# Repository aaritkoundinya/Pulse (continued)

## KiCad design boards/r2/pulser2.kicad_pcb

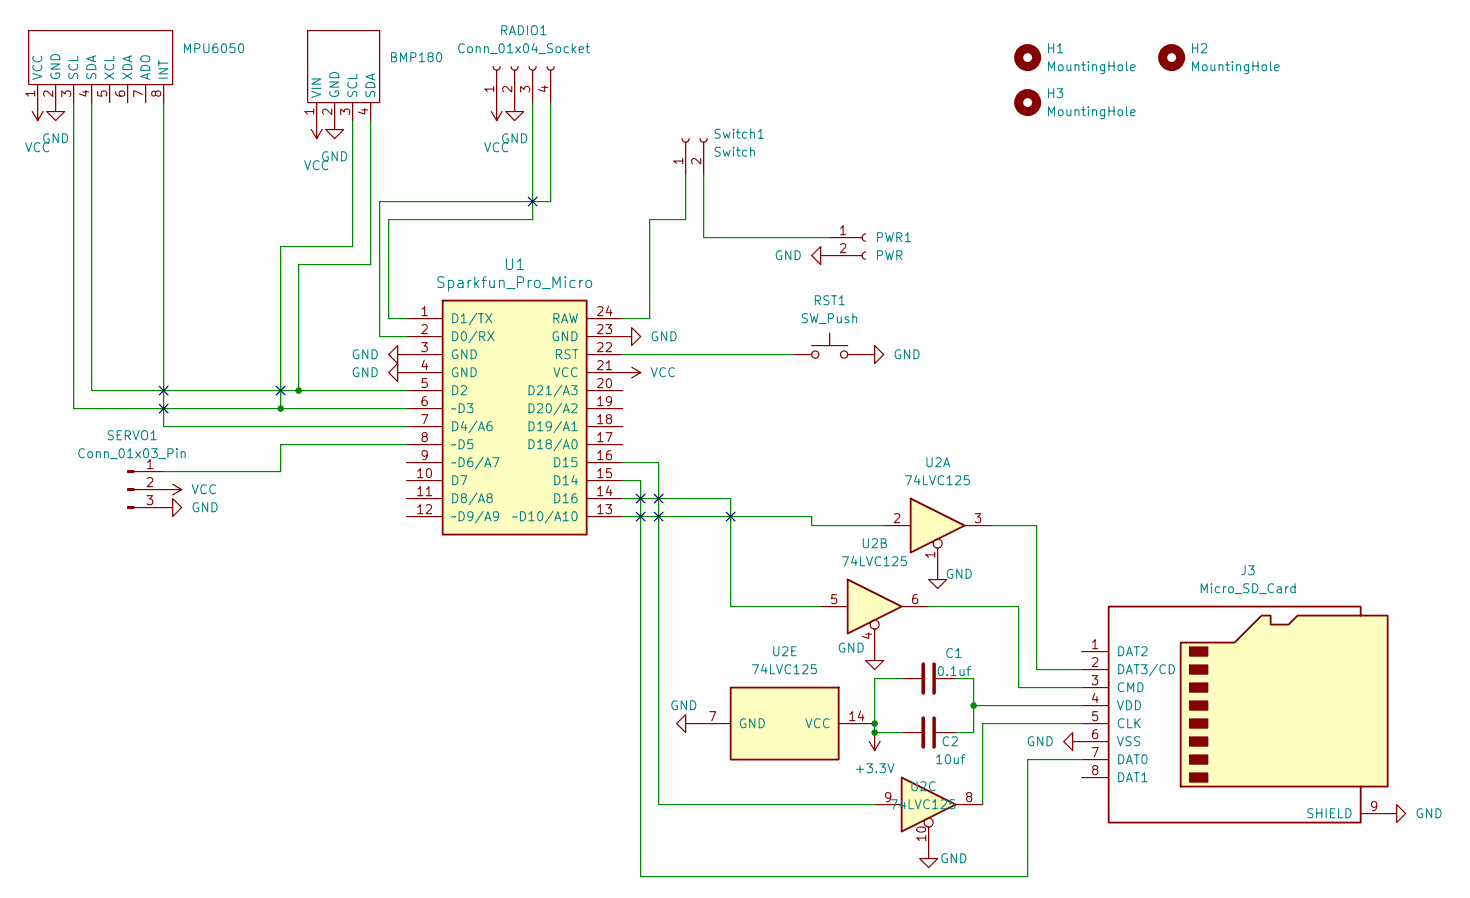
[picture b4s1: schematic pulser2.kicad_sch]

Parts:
BMP180: bmp180
C1: 0.1uf; C_0603_1608Metric_Pad1.08x0.95mm_HandSolder
C2: 10uf; C_0805_2012Metric_Pad1.18x1.45mm_HandSolder
H1, H2, H3: MountingHole; MountingHole_2.2mm_M2
J3: Micro_SD_Card; microSD_HC_Hirose_DM3D-SF
MPU6050: gy521
PWR1: PWR; JST_XH_B2B-XH-A_1x02_P2.50mm_Vertical
RADIO1: Conn_01x04_Socket; JST_XH_B4B-XH-A_1x04_P2.50mm_Vertical
RST1: SW_Push; SW_PUSH_6mm_H5mm
SERVO1: Conn_01x03_Pin; PinHeader_1x03_P2.54mm_Horizontal
Switch1: Switch; JST_XH_B2B-XH-A_1x02_P2.50mm_Vertical
U1: Sparkfun_Pro_Micro
U2: 74LVC125; SOIC-14_3.9x8.7mm_P1.27mm

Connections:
+3.3V: C1.2, C2.2, U2.14 (VCC)
GND: BMP180.2 (GND), J3.6 (VSS), J3.9 (SHIELD), MPU6050.2 (GND), PWR1.2, RADIO1.2, RST1.2, SERVO1.3, U1.3 (GND), U1.4 (GND), U1.23 (GND), U2.1, U2.4, U2.7 (GND), U2.10
unnamed: BMP180.3 (SCL), MPU6050.3 (SCL), U1.6 (~D3)
unnamed: BMP180.4 (SDA), MPU6050.4 (SDA), U1.5 (D2)
unnamed: J3.5 (CLK), U2.8
unnamed: J3.3 (CMD), U2.6
unnamed: J3.7 (DAT0), U1.15 (D14)
unnamed: J3.2 (DAT3/CD), U2.3
unnamed: C1.1, C2.1, J3.4 (VDD)
unnamed: MPU6050.8 (INT), U1.7 (D4/A6)
unnamed: PWR1.1, Switch1.2
unnamed: RADIO1.3, U1.1 (D1/TX)
unnamed: RADIO1.4, U1.2 (D0/RX)
unnamed: SERVO1.1, U1.8 (~D5)
unnamed: Switch1.1, U1.24 (RAW)
unnamed: U1.16 (D15), U2.9
unnamed: U1.14 (D16), U2.5
unnamed: RST1.1, U1.22 (RST)
unnamed: U1.13 (~D10/A10), U2.2
VCC: BMP180.1 (VIN), MPU6050.1 (VCC), RADIO1.1, SERVO1.2, U1.21 (VCC)

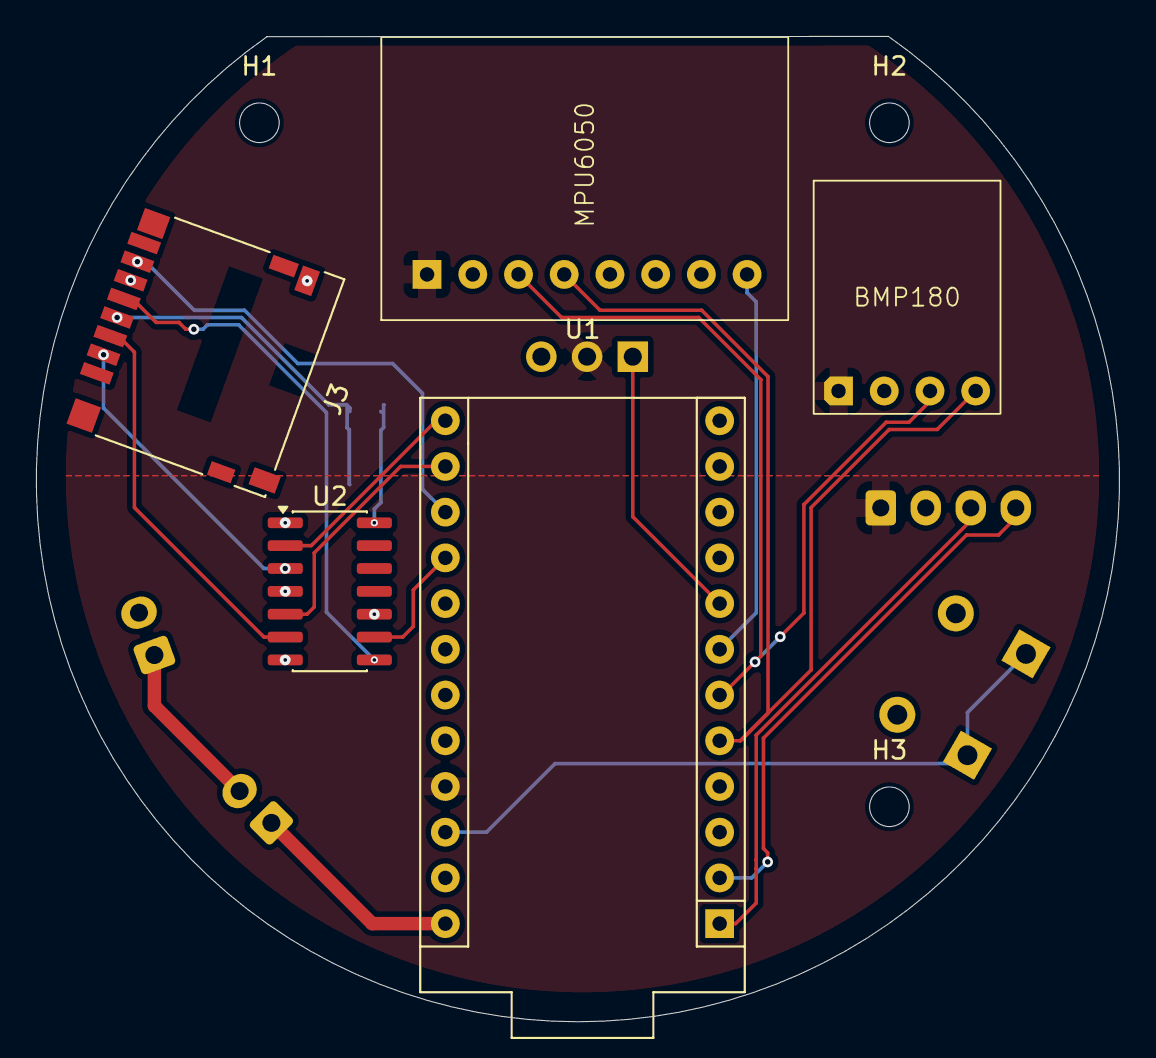
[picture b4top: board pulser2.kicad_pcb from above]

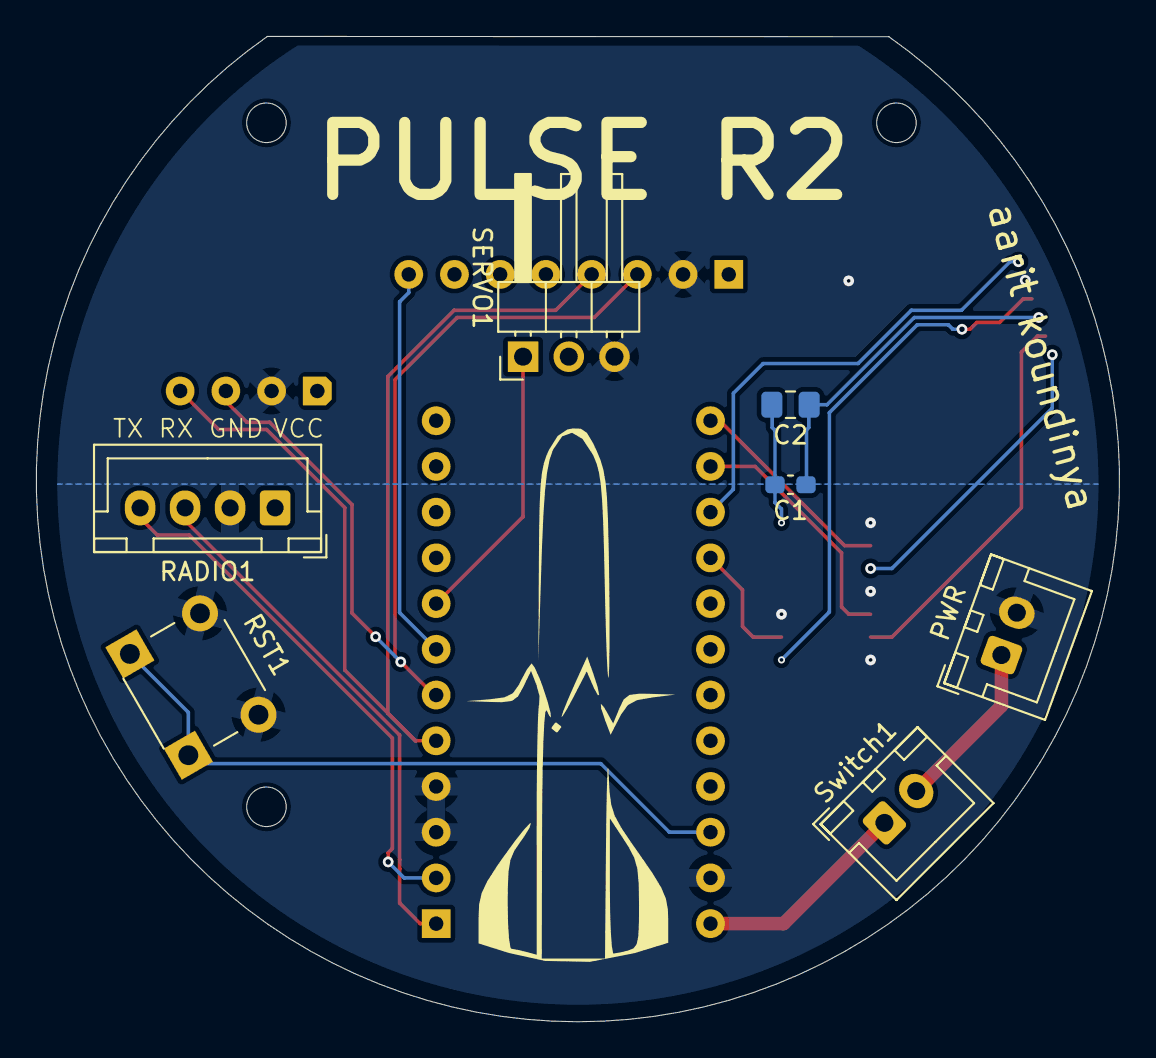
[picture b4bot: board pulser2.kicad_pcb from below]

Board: 2 copper layers, 60.2 x 54.7 mm, 15 parts (7 on the bottom side), 20 nets.

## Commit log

2026-04-16 Initial Pulse repo with r2 and r2.1 revisions
2026-04-16 added pulser3 - revised layout of pulse r2.1
2026-05-21 Update pulser3 board files
